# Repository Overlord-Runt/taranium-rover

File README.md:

# Taranium Rover
Made By Overlord Runt // Taran The Idiot

## Taranium Rover
This is an RC car I made for Hack Club's [Highway](https://highway.hackclub.com). It has a 4WD system and can turn with all 4 wheels. It uses ESP32 and ESPNow to communicate between the car and the controller

## The Car

### CAD
Majority of this project was getting the cadding of all the different parts done. This isnt what normal custom RC Cars look like and thats because everyone uses the exact same optimal design but I want to make and design something myself. idrc about the "optimal way" cuz where is the fun in that.

This thing is really big so you need like a lot of plates if you want to build it. Roughly about 6 plates and 40 hours of non stop printing.

It uses a crap ton of M3 screws and heatsets, so make sure you stock up on those

### Engineering
So bunch of enginnering went into this design. First the turning system. the 2 front wheels turn separately to allow for differential steering and reduced drag. It also allows me to use weaker and smaller 9g servos that are able to turn one wheel, but not 2.\
It used steel dowels to hold the pieces together and to ensure minimal friction between parts(make it turn stronger)

The bottom piece is there for stability and to make sure the wheel mount doesnt collapse.\
The suspensions are a bunch of high strendth springs that help distribute the weight of the whole car evenly through the wheels and absorb large bumps.\
\

The gear system uses a 16:1 gear down from the 12 000 rpm motor to give a 750 rpm spin under no load with roughly 6-10 Kgcm torque. under load it will have about 4-500 rpm and go about 1m/s. I use a large amount of bearings and steel rods in this design. For assembly, use a grinder to chop the steel rods into all the different lengths needed. You can refer to Full-Build.step in the CAD folder to see how everything is put together.

### PCB / Wiring Diagrams

The PCB didnt really take too long but I did have to make many different revisions to get here that did end up taking a lot of time.\
I wanted this to be somewhat of a universal mainboard that could be used in multiple use cases. Which is why I included space for stepper motor drivers. specifically the A4988. as well as 3 places for servos

The PCB features 2 BTS7960 motor drivers. They have 8 pins that connect to the boards(mounted externally). The mainboard also has space to use A4988 stepper motor drivers if you wish to swap out the 775s for stepper motors. 

I didnt have a footprint for the esp32 board that I am using so I just used 2 header pins and separated them the distance that it said on the datasheet.

this is the pinout for the Motor driver. it mathces that on the pcb so its an easy connection there

This is how you connect the motor driver to the battery and to the motor.

## The Controller

### CAD
The controller was fairly easy to cad. it uses M3 screws to hold itself together.

The triggers are just extensions to the buttons with a small indent to act as a stabiliser

The joysticks/encoder rods are cool in that I didn't use the revolve tool to make them. just a bunch of extrusions, drafts, and fillets.

Then in order to make it actually buildable, i chopped off the end and added a dowel

### PCB
For the pcb I wanted to keep it basic. So 2 encoders. One for speed, other for turning. then 2 buttons. one to reverse, other for anything else you might wanna add in the future.\
\
Its a cool design if you ask me and it does its job.\

## Firmware

uses espnow and you can find the firmware in the firmware folders. the names should tell you all you need to knwo about which on goes to which but for those who are a little slow, controller.ino flashes to the controller and mainboard.ino flashes to the mainboard

## How To Build

1. Print out all parts
2. Insert heatsets into all parts
3. Solder circuit boards as shown in schematics
4. assemble internal structures such as the turning system
5. Slide connectors onto rods then use rods to connect 2 internals sides
6. Attach chasis frames beginning with the parts that connect to the frame.
7. Flash esp with code
8. mount pcb of top panel
9. insert battery and sercure it down with screws
10. screw on top panels
11. flash controller with code
12. solder pcb
13. attach first part of the sticks to encoders
14. mount pcb to case
15. attach second part of sticks to encoders and use super glue or hot glue to hold it down
16. screw back panel
17. play enjoy.

If i forgot something I will add it on when I build

## BOM

|Name|QTY|Cost(AUD)|Cost(USD)|Link|
|----|---|---------|---------|----|
|3s 2.2AH LiPo|1|$47.19||[LINK](https://www.amazon.com.au/gp/product/B09NXM2DW4/ref=sw_img_1?smid=A3S3YJCXW342CA&psc=1)|
|ESP32 Dev Board|2|$7.39||[LINK](https://www.aliexpress.com/item/1005008499671222.html?spm=a2g0o.cart.0.0.440338dajzfCE9&mp=1&pdp_npi=5%40dis%21AUD%21AUD%207.95%21AUD%207.39%21%21AUD%207.25%21%21%21%402103273e17519916653746516e9cc4%2112000045428891808%21ct%21AU%216138339337%21%211%210)|
|Buck Converter|1|$1.47||[LINK](https://www.aliexpress.com/item/1005006365697021.html?spm=a2g0o.cart.0.0.7b7238daocpVDw&mp=1&pdp_npi=5%40dis%21AUD%21AUD%201.52%21AUD%201.47%21%21AUD%201.47%21%21%21%402101c80017519920616365587e7ede%2112000036911557265%21ct%21AU%216138339337%21%211%210)|
|Steel Rods|1|$13.59||[LINK](https://www.aliexpress.com/item/1005005041338002.html?spm=a2g0o.cart.0.0.7b7238daocpVDw&mp=1&pdp_npi=5%40dis%21AUD%21AUD%2013.59%21AUD%2013.59%21%21AUD%2013.59%21%21%21%402101c80017519920616365587e7ede%2112000031424484647%21ct%21AU%216138339337%21%211%210)|
|775 12V DC Motor|2|$31.40|20.2|[LINK](https://www.aliexpress.com/item/1005006573459459.html?spm=a2g0o.cart.0.0.7c6438da8p7SyB&mp=1&pdp_npi=5%40dis%21AUD%21AUD%2015.69%21AUD%2015.69%21%21AUD%2015.69%21%21%21%402103244417540105652123591ed7b3%2112000037708674071%21ct%21AU%216138339337%21%212%210)|
|BTS7960 Motor Driver|2|$15.00|9.65|[LINK](https://www.aliexpress.com/item/1005007091280016.html?spm=a2g0o.cart.0.0.7c6438da8p7SyB&mp=1&pdp_npi=5%40dis%21AUD%21AUD%207.49%21AUD%207.49%21%21AUD%207.49%21%21%21%402103244417540105652123591ed7b3%2112000039368243485%21ct%21AU%216138339337%21%212%210)|
|Header Pins|1|$2.54||[LINK](https://www.aliexpress.com/item/1005006034877497.html?spm=a2g0o.productlist.main.10.11f92012N9AGjn&algo_pvid=01056414-a579-4c66-8c0f-8c11b43bcf9c&algo_exp_id=01056414-a579-4c66-8c0f-8c11b43bcf9c-9&pdp_ext_f=%7B%22order%22%3A%221565%22%2C%22eval%22%3A%221%22%7D&pdp_npi=4%40dis%21AUD%212.53%212.53%21%21%2111.63%2111.63%21%402103273e17519925834072774e9c9c%2112000035419985198%21sea%21AU%216138339337%21X&curPageLogUid=1HjffVUnlIhg&utparam-url=scene%3Asearch%7Cquery_from%3A)|
|Servo Motor 5V|2|$4.69||[LINK](https://www.aliexpress.com/item/1005006572297006.html?spm=a2g0o.productlist.main.7.66d4e9c1BLk6SW&algo_pvid=e72cc098-c504-4e33-aae5-d6b7896ada10&algo_exp_id=e72cc098-c504-4e33-aae5-d6b7896ada10-6&pdp_ext_f=%7B%22order%22%3A%224516%22%2C%22eval%22%3A%221%22%7D&pdp_npi=4%40dis%21AUD%214.69%214.69%21%21%213.01%213.01%21%402101c5bf17519927191303065e98d7%2112000037705759120%21sea%21AU%216138339337%21X&curPageLogUid=bn0XkIYGxz4A&utparam-url=scene%3Asearch%7Cquery_from%3A)|
|M3x10mm Screws||$2.82||[LINK](https://www.aliexpress.com/item/32810852732.html?spm=a2g0o.order_list.order_list_main.28.74441802cg1DM1)|
|M3x16mm Screws||$3.43||[LINK](https://www.aliexpress.com/item/32810852732.html?spm=a2g0o.order_list.order_list_main.28.74441802cg1DM1)|
|M3x6mm Screws||$2.29||[LINK](https://www.aliexpress.com/item/32810852732.html?spm=a2g0o.order_list.order_list_main.28.74441802cg1DM1)|
|M3D5L6 Heatsets|45|$3.82||[LINK](https://www.aliexpress.com/item/1005003582355741.html?spm=a2g0o.order_list.order_list_main.45.21221802z3BMxP)|
|M3 Steel Dowels 20mm|4|$2.47||[LINK](https://www.aliexpress.com/item/1005003990055624.html?spm=a2g0o.cart.0.0.7c6438da8p7SyB&mp=1&pdp_npi=5%40dis%21AUD%21AUD%202.55%21AUD%202.55%21%21AUD%202.55%21%21%21%402103201917539747613531159ef006%2112000027659580374%21ct%21AU%216138339337%21%211%210)|
|M3 Steel Dowels 12mm|2|$2.41||[LINK](https://www.aliexpress.com/item/1005003990055624.html?spm=a2g0o.cart.0.0.7c6438da8p7SyB&mp=1&pdp_npi=5%40dis%21AUD%21AUD%202.55%21AUD%202.55%21%21AUD%202.55%21%21%21%402103201917539747613531159ef006%2112000027659580374%21ct%21AU%216138339337%21%211%210)|
|M4 Steel Dowels 12mm|2|$2.47||[LINK](https://www.aliexpress.com/item/1005003990055624.html?spm=a2g0o.cart.0.0.7c6438da8p7SyB&mp=1&pdp_npi=5%40dis%21AUD%21AUD%202.55%21AUD%202.55%21%21AUD%202.55%21%21%21%402103201917539747613531159ef006%2112000027659580374%21ct%21AU%216138339337%21%211%210)|
|M5 Steel Dowels 25mm|2|$3.16||[LINK](https://www.aliexpress.com/item/1005003990055624.html?spm=a2g0o.cart.0.0.7c6438da8p7SyB&mp=1&pdp_npi=5%40dis%21AUD%21AUD%202.55%21AUD%202.55%21%21AUD%202.55%21%21%21%402103201917539747613531159ef006%2112000027659580374%21ct%21AU%216138339337%21%211%210)|
|Car Mainboard|1|9.18|$6.90|JLCPCB|
|Controller Board|1|15.1|$9.87|JLCPCB|
|3d Printed parts||||I aint counting how many there are|
|LiPo Balance Charger|1|$23.95||[LINK](https://www.amazon.com.au/Jinming-Battery-Balance-Charger-Blaster/dp/B07JDG4D8W/ref=sr_1_7?crid=2QSVU4PIMQWEP&dib=eyJ2IjoiMSJ9.egVEYVMdFeiJ7Rp5U0GsW3MPCFjH2JppaEegY-6QF1ybXfPnuH7ehcqwsalxISOPBUoZ68yW8V0V9EmSkjSAxz8C7UdrdUezt6iJ5_6-ePqY1OympOLNnzXOyxJhWJ2sCB3tMHHNAahfemRGOHYjULgd62YWGpVJWYwXsBrbpyq5Tr_IyYgdJclzJoRmBvqXEjzY5W0FZaIy_gxmmjxeAksaYQ1llEEbxFEoMpw1EkxXsO2L39F73PxA1ek0gpCMQTNUQ-N5_VKgioZNR_3n90hGdIGBqGgcM8sjdCRed0g.5tzFgGdyR7y_fjpOhZMOOhIfYhpp-g9E6b3zGECYRn8&dib_tag=se&keywords=zeee+3S+lipo+balance+charger&qid=1752048546&sprefix=zeee3s+lipo+balance+charger%2Caps%2C554&sr=8-7)|
|Horizontal Rotary Encoder|2|$4.90||[LINK](https://www.aliexpress.com/item/1005006128388016.html?spm=a2g0o.productlist.main.6.68807HYA7HYAsY&algo_pvid=b1d8a2b1-697b-4cdf-a5ac-84e7fe9106d6&algo_exp_id=b1d8a2b1-697b-4cdf-a5ac-84e7fe9106d6-5&pdp_ext_f=%7B%22order%22%3A%2261%22%2C%22eval%22%3A%221%22%7D&pdp_npi=4%40dis%21AUD%213.00%213.00%21%21%211.93%211.93%21%40210318e817520645594814154ebb46%2112000035886812807%21sea%21AU%216138339337%21X&curPageLogUid=BApYx7Hqtu0n&utparam-url=scene%3Asearch%7Cquery_from%3A)|
|T-plug connector|1|$2.61||[LINK](https://www.aliexpress.com/item/4001212535096.html?spm=a2g0o.detail.0.0.1a35IjAXIjAXdN&mp=1&pdp_npi=5%40dis%21AUD%21AUD%202.61%21AUD%202.61%21%21AUD%202.61%21%21%21%40210318e817520646010564484ebb6d%2110000015320231372%21ct%21AU%216138339337%21%211%210)|
|10 gauge wire|2m|$15.45||[LINK](https://www.aliexpress.com/item/1005007759043423.html?spm=a2g0o.detail.0.0.7927Shi1Shi1fd&mp=1&pdp_npi=5%40dis%21AUD%21AUD%2028.91%21AUD%2015.42%21%21AUD%2015.42%21%21%21%402103273e17540187523768582eab2f%2112000042200258296%21ct%21AU%216138339337%21%211%210)|
|3.7V lipo|1|$14.99||[LINK](https://www.amazon.com.au/gp/product/B09R7F1VV5/ref=sw_img_1?smid=A12788XRWB37UE&th=1)|
|XH 2.54 Male connector|1|$1.79||[LINK](https://www.aliexpress.com/item/1005007460897865.html?spm=a2g0o.productlist.main.3.64b0209u209ugB&algo_pvid=b5ea3270-3fea-44d1-ac17-8cbea19e97f6&algo_exp_id=b5ea3270-3fea-44d1-ac17-8cbea19e97f6-2&pdp_ext_f=%7B%22order%22%3A%226726%22%2C%22eval%22%3A%221%22%7D&pdp_npi=4%40dis%21AUD%211.79%211.79%21%21%211.15%211.15%21%402101d9ee17520717044885071e1aac%2112000040853255020%21sea%21AU%216138339337%21X&curPageLogUid=cFIm27cGLruP&utparam-url=scene%3Asearch%7Cquery_from%3A)|
|6mm switch|2|$2.89||[LINK](https://www.aliexpress.com/item/1005004971266223.html?spm=a2g0o.cart.0.0.68dc38datwPIHU&mp=1&pdp_npi=5%40dis%21AUD%21AUD%202.89%21AUD%202.89%21%21AUD%202.83%21%21%21%402103277f17520760612977156e2f93%2112000031200483146%21ct%21AU%216138339337%21%211%210&pdp_ext_f=%7B%22cart2PdpParams%22%3A%7B%22pdpBusinessMode%22%3A%22retail%22%7D%7D)|
|Hardened Springs|4|||sourced from my dad|
|1kg PLA|1||||
|1kg PETG|1||||
|Boost Converter|1|$4.83||[LINK](https://www.aliexpress.com/item/1005008447199869.html?spm=a2g0o.cart.0.0.440338daUp0LxT&mp=1&pdp_npi=5%40dis%21AUD%21AUD%205.10%21AUD%204.83%21%21AUD%204.83%21%21%21%402101e9ec17530288048031105ed1c8%2112000045180678408%21ct%21AU%216138339337%21%211%210)|
|SSD1306 128x64 OLED Display|1|$4.20||[LINK](https://www.aliexpress.com/item/1005009243034318.html?spm=a2g0o.cart.0.0.440338daUp0LxT&mp=1&pdp_npi=5%40dis%21AUD%21AUD%209.33%21AUD%204.20%21%21AUD%204.20%21%21%21%402101e9ec17530288048031105ed1c8%2112000048446306499%21ct%21AU%216138339337%21%211%210)|
|TOTAL||$246.03|$161.03||

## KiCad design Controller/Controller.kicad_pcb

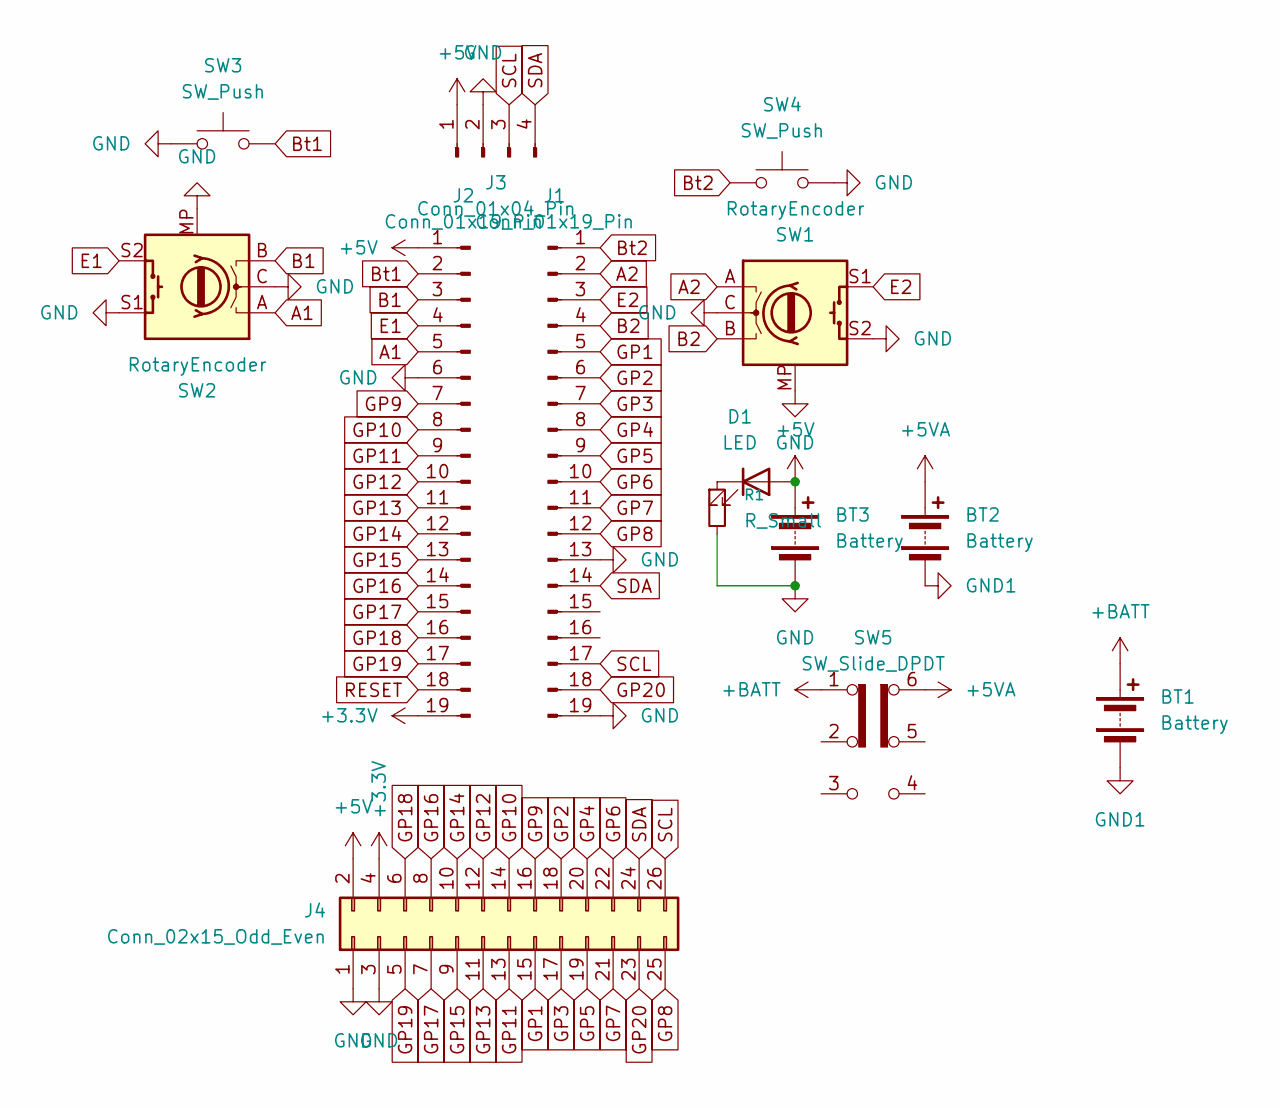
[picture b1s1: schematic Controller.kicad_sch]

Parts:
BT1: Battery; JST_XH_B2B-XH-A_1x02_P2.50mm_Vertical
BT2, BT3: Battery; PinSocket_1x02_P2.54mm_Vertical
D1: LED; LED_D3.0mm
J1, J2: Conn_01x19_Pin; PinSocket_1x19_P2.54mm_Vertical
J3: Conn_01x04_Pin; MODULE_DM-OLED096-636
J4: Conn_02x15_Odd_Even; PinHeader_2x13_P2.54mm_Vertical
R1: R_Small; R_Axial_DIN0204_L3.6mm_D1.6mm_P5.08mm_Horizontal
SW1, SW2: RotaryEncoder; EC11-Horizontal
SW3, SW4: SW_Push; Button-6mm-2pin-tht
SW5: SW_Slide_DPDT; SW_E-Switch_EG1271_SPDT

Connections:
+3.3V: J2.19, J4.4
+5V: BT3.1 (+), D1.2 (A), J2.1, J3.1, J4.2
+5VA: BT2.1 (+), SW5.6 (C)
+BATT: BT1.1 (+), SW5.1 (A)
A1: J2.5, SW2.A
A2: J1.2, SW1.A
B1: J2.3, SW2.B
B2: J1.4, SW1.B
Bt1: J2.2, SW3.2
Bt2: J1.1, SW4.1
E1: J2.4, SW2.S2
E2: J1.3, SW1.S1
GND: BT3.2 (-), J1.13, J1.19, J2.6, J3.2, J4.1, J4.3, R1.2, SW1.C, SW1.MP, SW1.S2, SW2.C, SW2.MP, SW2.S1, SW3.1, SW4.2
GND1: BT1.2 (-), BT2.2 (-)
GP1: J1.5, J4.15
GP2: J1.6, J4.18
GP3: J1.7, J4.17
GP4: J1.8, J4.20
GP5: J1.9, J4.19
GP6: J1.10, J4.22
GP7: J1.11, J4.21
GP8: J1.12, J4.25
GP9: J2.7, J4.16
GP10: J2.8, J4.14
GP11: J2.9, J4.13
GP12: J2.10, J4.12
GP13: J2.11, J4.11
GP14: J2.12, J4.10
GP15: J2.13, J4.9
GP16: J2.14, J4.8
GP17: J2.15, J4.7
GP18: J2.16, J4.6
GP19: J2.17, J4.5
GP20: J1.18, J4.23
unnamed: D1.1 (K), R1.1
RESET: J2.18
SCL: J1.17, J3.3, J4.26
SDA: J1.14, J3.4, J4.24

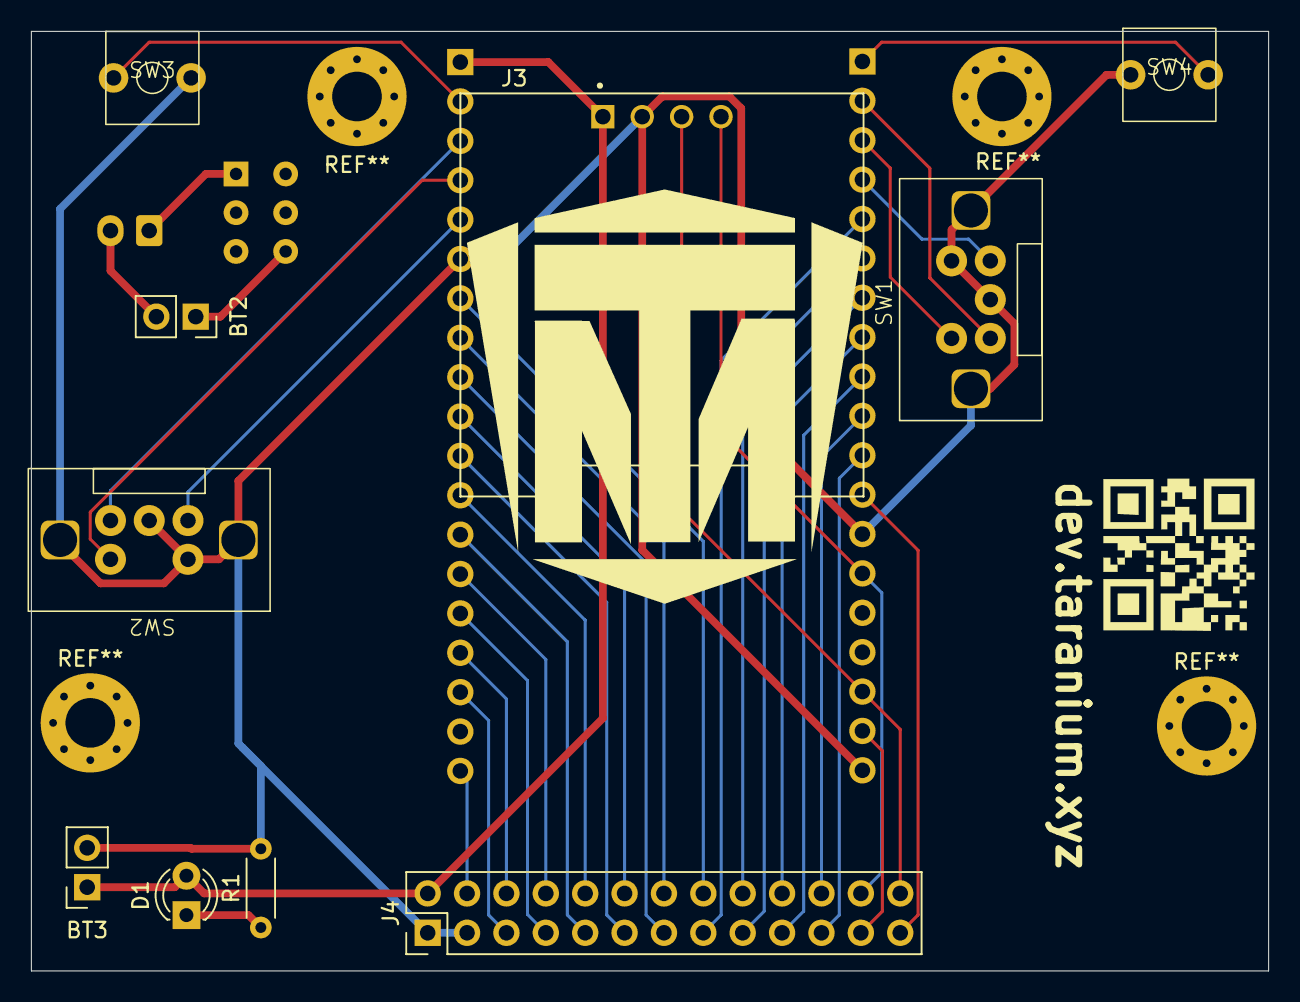
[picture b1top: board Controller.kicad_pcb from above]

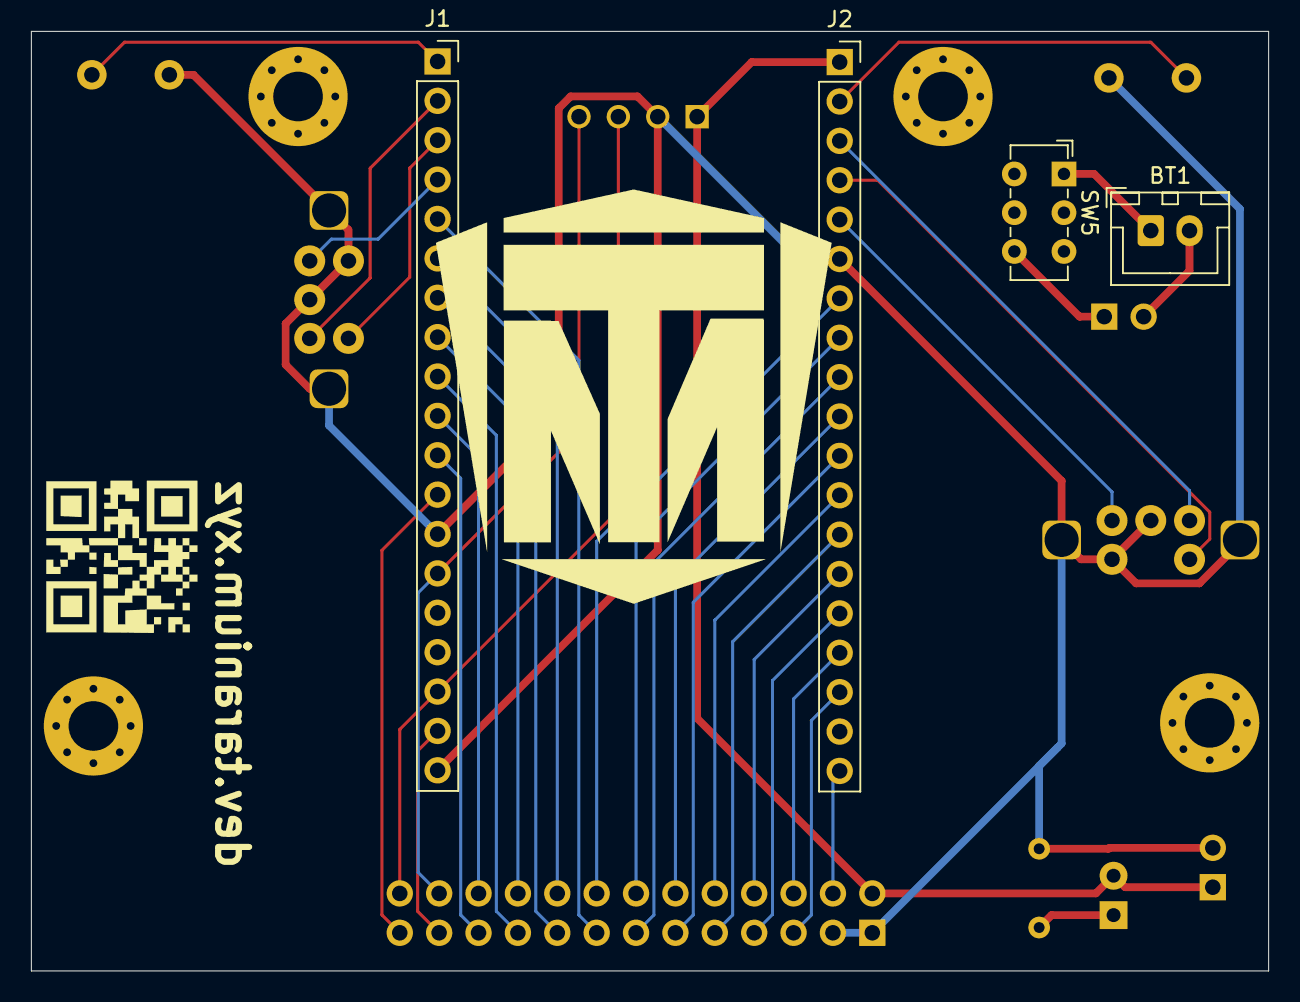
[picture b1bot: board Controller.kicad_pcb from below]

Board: 2 copper layers, 79.8 x 60.6 mm, 14 parts (4 on the bottom side), 37 nets.

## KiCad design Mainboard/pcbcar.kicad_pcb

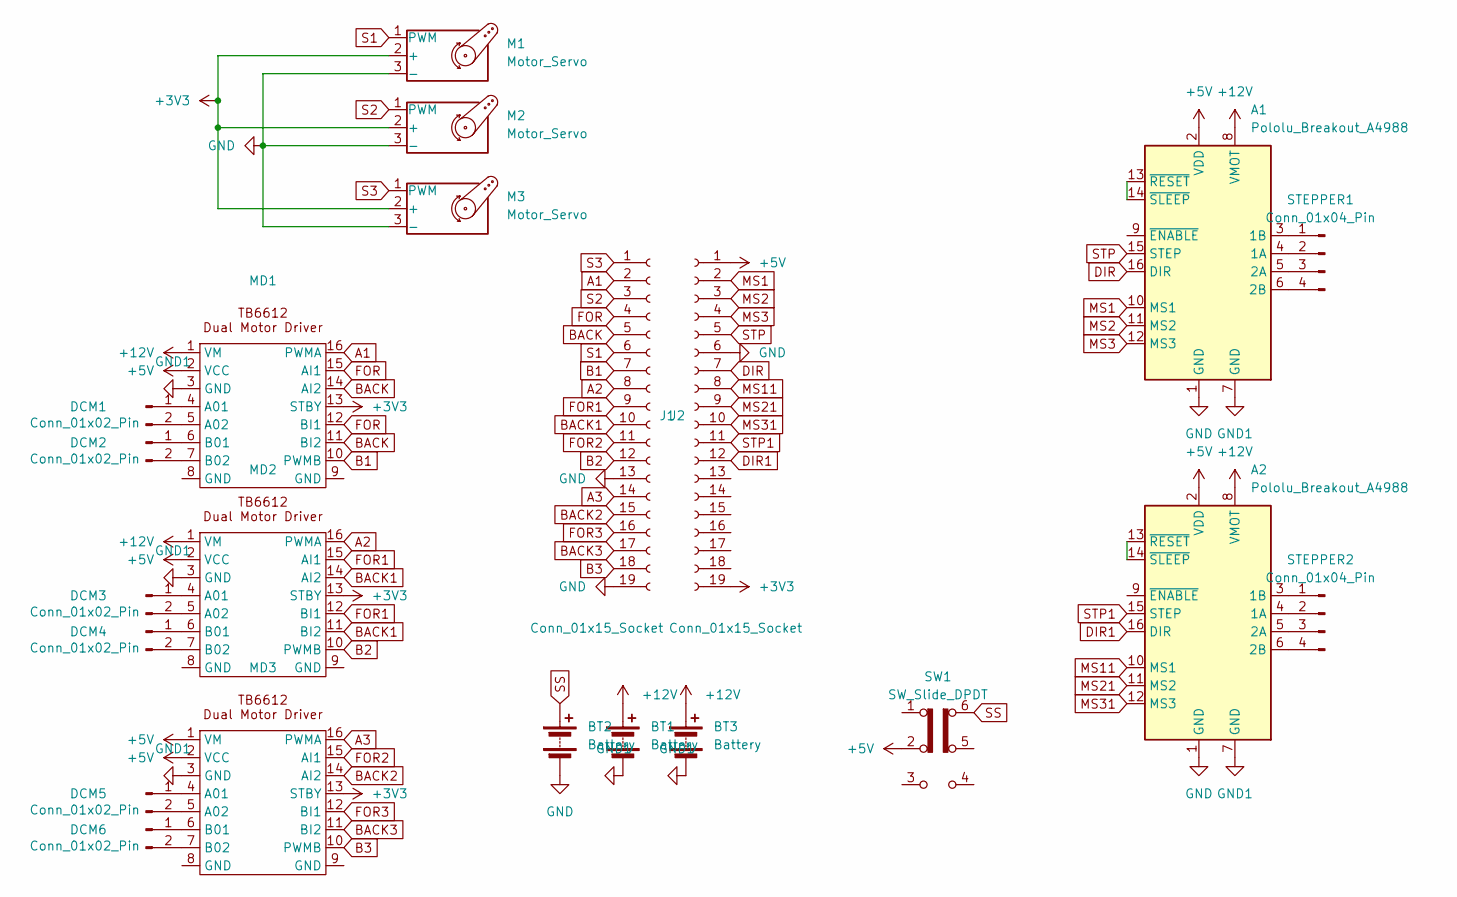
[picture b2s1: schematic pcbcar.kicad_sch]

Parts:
A1, A2: Pololu_Breakout_A4988; Pololu_Breakout-16_15.2x20.3mm
BT1, BT2, BT3: Battery; PinHeader_1x02_P2.54mm_Vertical
DCM1, DCM2, DCM3, DCM4, DCM5, DCM6: Conn_01x02_Pin; PinHeader_1x02_P2.54mm_Vertical
J1, J2: Conn_01x15_Socket; PinHeader_1x19_P2.54mm_Vertical
M1, M2, M3: Motor_Servo; PinHeader_1x03_P2.54mm_Vertical
MD1, MD2, MD3: MODULE_ROB-14450
STEPPER1, STEPPER2: Conn_01x04_Pin; PinHeader_1x04_P2.54mm_Vertical
SW1: SW_Slide_DPDT; SW_E-Switch_EG1271_SPDT

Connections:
+3V3: J2.19, M1.2 (+), M2.2 (+), M3.2 (+), MD1.13 (STBY), MD2.13 (STBY), MD3.13 (STBY)
+5V: A1.2 (VDD), A2.2 (VDD), J2.1, MD1.2 (VCC), MD2.2 (VCC), MD3.1 (VM), MD3.2 (VCC), SW1.2 (B)
+12V: A1.8 (VMOT), A2.8 (VMOT), BT1.1 (+), BT3.1 (+), MD1.1 (VM), MD2.1 (VM)
A1: J1.2, MD1.16 (PWMA)
A2: J1.8, MD2.16 (PWMA)
A3: J1.14, MD3.16 (PWMA)
B1: J1.7, MD1.10 (PWMB)
B2: J1.12, MD2.10 (PWMB)
B3: J1.18, MD3.10 (PWMB)
BACK: J1.5, MD1.11 (BI2), MD1.14 (AI2)
BACK1: J1.10, MD2.11 (BI2), MD2.14 (AI2)
BACK2: J1.15, MD3.14 (AI2)
BACK3: J1.17, MD3.11 (BI2)
DIR: A1.16 (DIR), J2.7
DIR1: A2.16 (DIR), J2.12
FOR: J1.4, MD1.12 (BI1), MD1.15 (AI1)
FOR1: J1.9, MD2.12 (BI1), MD2.15 (AI1)
FOR2: J1.11, MD3.15 (AI1)
FOR3: J1.16, MD3.12 (BI1)
GND: A1.1 (GND), A2.1 (GND), BT2.2 (-), J1.13, J1.19, J2.6, M1.3 (-), M2.3 (-), M3.3 (-)
GND1: A1.7 (GND), A2.7 (GND), BT1.2 (-), BT3.2 (-), MD1.3 (GND), MD2.3 (GND), MD3.3 (GND)
MS1: A1.10 (MS1), J2.2
MS2: A1.11 (MS2), J2.3
MS3: A1.12 (MS3), J2.4
MS11: A2.10 (MS1), J2.8
MS21: A2.11 (MS2), J2.9
MS31: A2.12 (MS3), J2.10
unnamed: A1.4 (1A), STEPPER1.2
unnamed: A1.3 (1B), STEPPER1.1
unnamed: A1.5 (2A), STEPPER1.3
unnamed: A1.6 (2B), STEPPER1.4
unnamed: A1.13 (~RESET), A1.14 (~SLEEP)
unnamed: A2.4 (1A), STEPPER2.2
unnamed: A2.3 (1B), STEPPER2.1
unnamed: A2.5 (2A), STEPPER2.3
unnamed: A2.6 (2B), STEPPER2.4
unnamed: A2.13 (~RESET), A2.14 (~SLEEP)
unnamed: DCM1.1, MD1.4 (A01)
unnamed: DCM1.2, MD1.5 (A02)
unnamed: DCM2.1, MD1.6 (B01)
unnamed: DCM2.2, MD1.7 (B02)
unnamed: DCM3.1, MD2.4 (A01)
unnamed: DCM3.2, MD2.5 (A02)
unnamed: DCM4.1, MD2.6 (B01)
unnamed: DCM4.2, MD2.7 (B02)
unnamed: DCM5.1, MD3.4 (A01)
unnamed: DCM5.2, MD3.5 (A02)
unnamed: DCM6.1, MD3.6 (B01)
unnamed: DCM6.2, MD3.7 (B02)
S1: J1.6, M1.1 (PWM)
S2: J1.3, M2.1 (PWM)
S3: J1.1, M3.1 (PWM)
SS: BT2.1 (+), SW1.6 (C)
STP: A1.15 (STEP), J2.5
STP1: A2.15 (STEP), J2.11

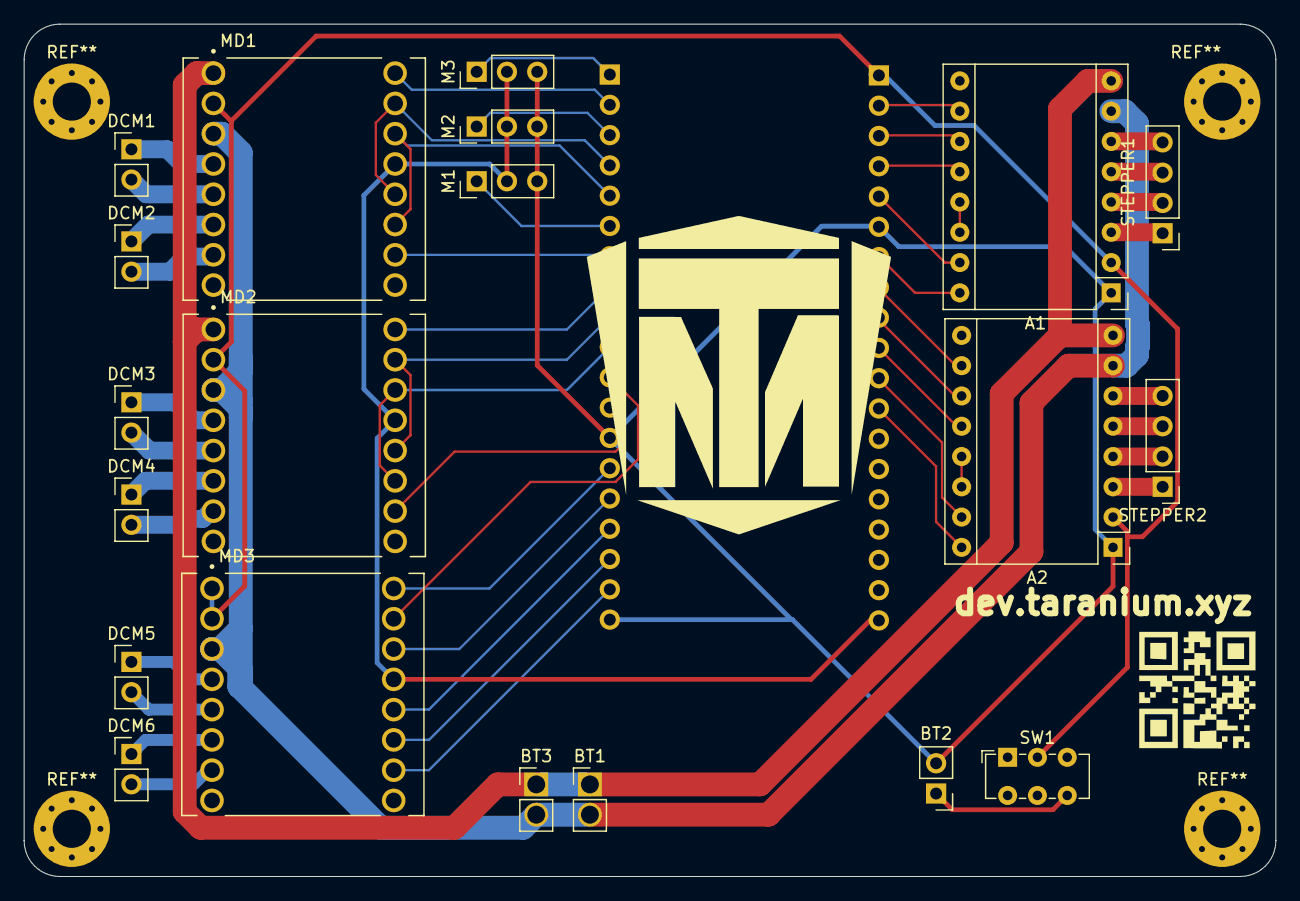
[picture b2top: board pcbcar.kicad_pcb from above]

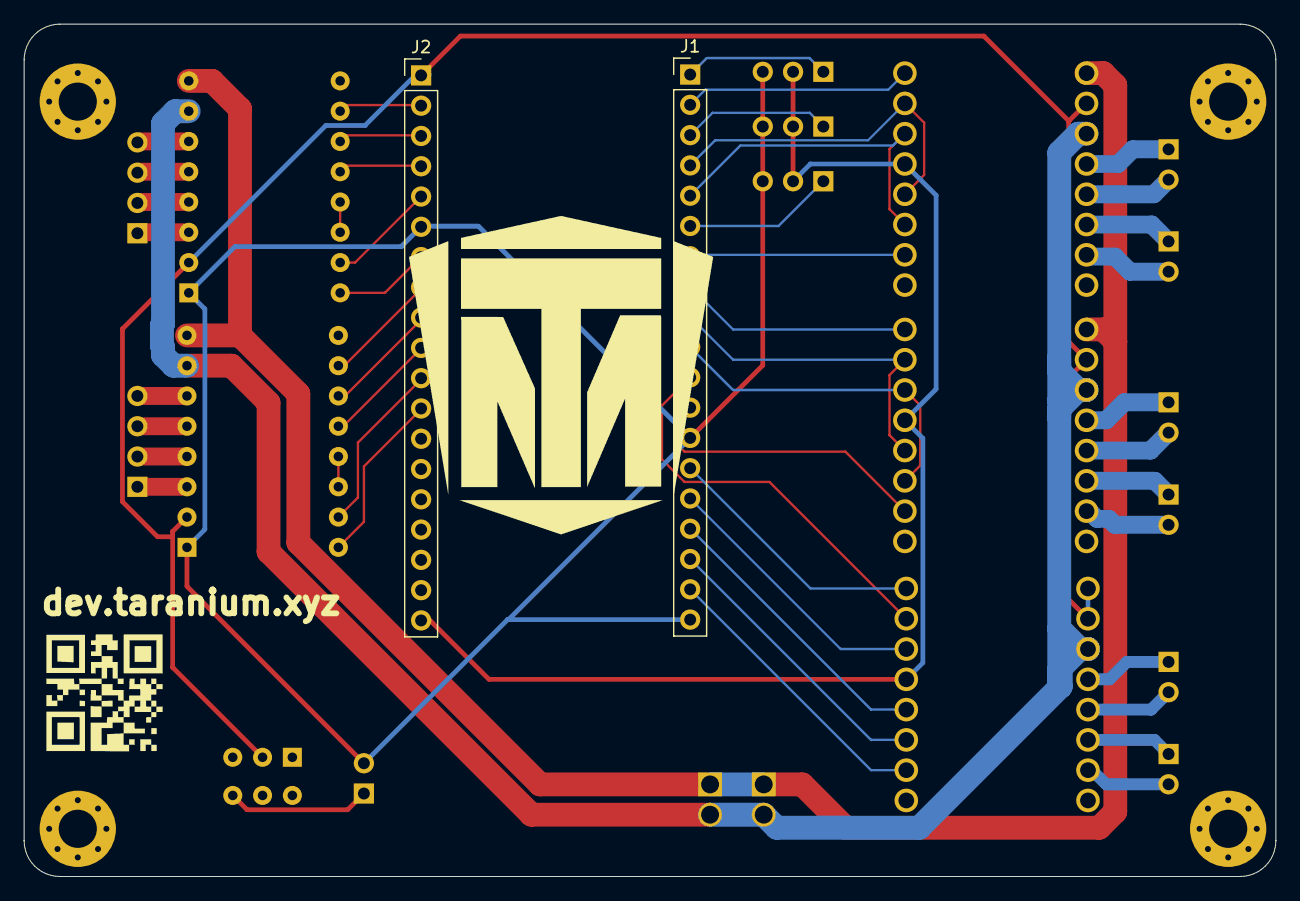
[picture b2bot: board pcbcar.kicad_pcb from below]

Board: 2 copper layers, 105.0 x 71.5 mm, 22 parts (2 on the bottom side), 55 nets.

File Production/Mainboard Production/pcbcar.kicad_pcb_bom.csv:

Designator,Quantity,Value,Footprint,Package,MPN,DNP,Mount_Type,Description
"A1, A2",2,Pololu_Breakout_A4988,Pololu_Breakout-16_15.2x20.3mm,,,,tht,"Pololu Breakout Board, Stepper Driver A4988"
"BT1, BT2, BT3",3,Battery,PinHeader_1x02_P2.54mm_Vertical,,,,tht,Multiple-cell battery
"DCM1, DCM2, DCM3, DCM4, DCM5, DCM6",6,Conn_01x02_Pin,PinHeader_1x02_P2.54mm_Vertical,,,,tht,"Generic connector, single row, 01x02, script generated"
"J1, J2",2,Conn_01x15_Socket,PinHeader_1x19_P2.54mm_Vertical,,,,tht,"Generic connector, single row, 01x19, script generated"
"M1, M2, M3",3,Motor_Servo,PinHeader_1x03_P2.54mm_Vertical,,,,tht,"Servo Motor (Futaba, HiTec, JR connector)"
"MD1, MD2, MD3",3,~,MODULE_ROB-14450,,,,tht,
"STEPPER1, STEPPER2",2,Conn_01x04_Pin,PinHeader_1x04_P2.54mm_Vertical,,,,tht,"Generic connector, single row, 01x04, script generated"
SW1,1,SW_Slide_DPDT,SW_E-Switch_EG1271_SPDT,,,,tht,"Slide Switch, dual pole double throw"

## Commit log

2025-05-15 Create CNAME
